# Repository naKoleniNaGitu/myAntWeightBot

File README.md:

# myAntWeightBot

## Sources

### Controler 
I decided to go with ESP32-S3 develoment module for control flexibility and BT connectivity.

* [waveshare.com product esp32-s3-zero.htm](https://www.waveshare.com/product/mcu-tools/development-boards/esp32/esp32-s3-zero.htm)
* [ESP32 S3 zero wiki](https://www.waveshare.com/wiki/ESP32-S3-Zero)

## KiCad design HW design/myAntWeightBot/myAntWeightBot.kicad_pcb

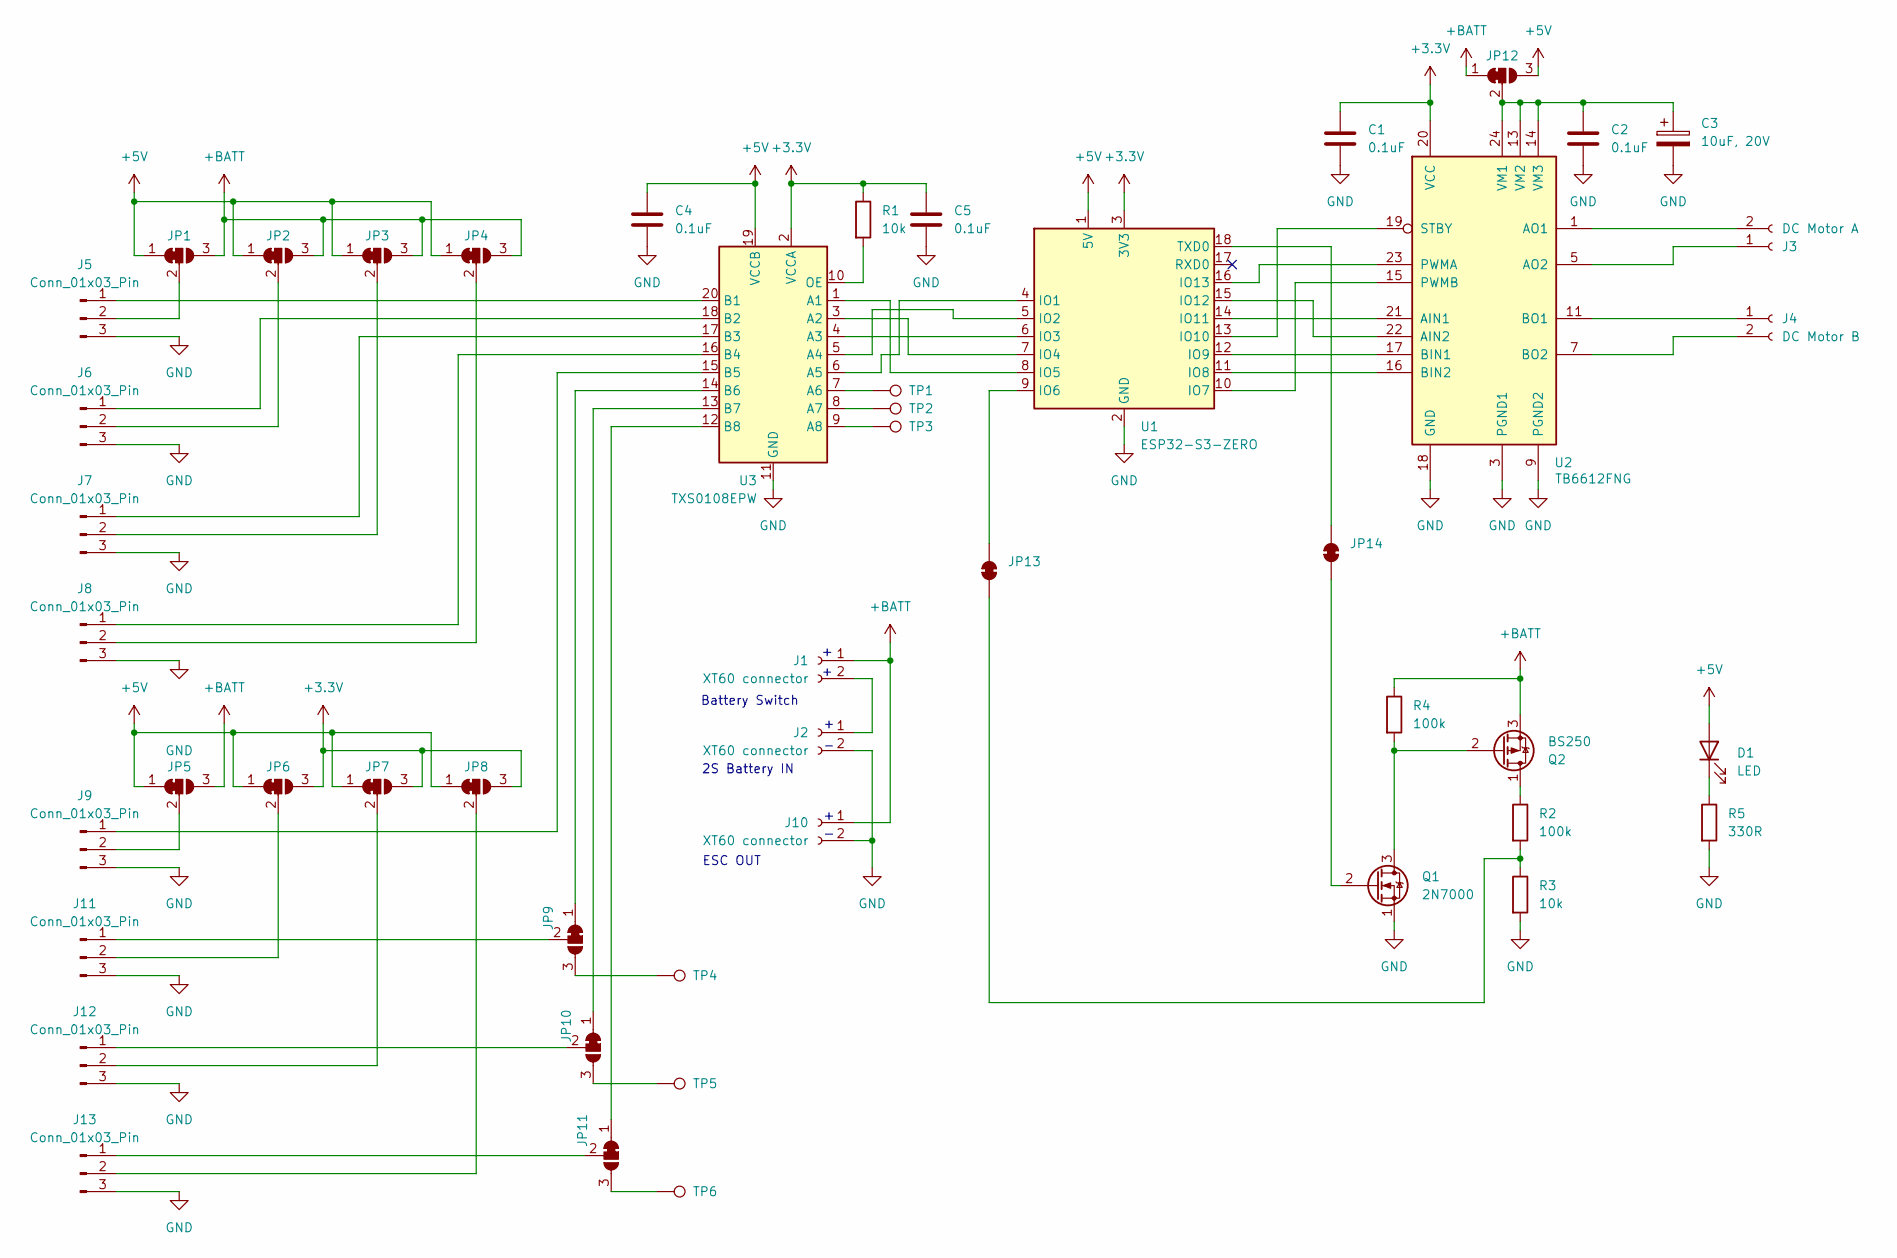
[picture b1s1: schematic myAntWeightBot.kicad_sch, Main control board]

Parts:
C1, C2, C4, C5: 0.1uF; C_0805_2012Metric
C3: 10uF, 20V; CP_EIA-6032-20_AVX-F
D1: LED; LED_D5.0mm
J1, J10: XT60 connector; XT60-F_1x02_P7.20mm_Horizontal_SMD
J2: XT60 connector; XT60-M_1x02_P7.20mm_Horizontal_SMD
J3: DC Motor A; PinHeader_1x02_P2.54mm_Vertical
J4: DC Motor B; PinHeader_1x02_P2.54mm_Vertical
J5, J6, J7, J8, J9, J11, J12, J13: Conn_01x03_Pin; PinHeader_1x03_P2.54mm_Vertical
JP1, JP2, JP3, JP4, JP5, JP6, JP7, JP8, JP9, JP10, JP11, JP12: SolderJumper_3_Bridged12; SolderJumper-3_P1.3mm_Bridged12_Pad1.0x1.5mm
JP13, JP14: SolderJumper_2_Bridged; SolderJumper-2_P1.3mm_Bridged_Pad1.0x1.5mm
Q1: 2N7000; TO-92_Inline_W4.0mm_Horizontal_FlatSideDown
Q2: BS250; TO-92_Inline_W4.0mm_Horizontal_FlatSideDown
R1, R3: 10k; R_0805_2012Metric
R2, R4: 100k; R_0805_2012Metric
R5: 330R; R_0805_2012Metric
TP1, TP2, TP3, TP4, TP5, TP6: TestPoint; TestPoint_THTPad_D1.5mm_Drill0.7mm
U1: ESP32-S3-ZERO
U2: TB6612FNG; SSOP-24_5.3x8.2mm_P0.65mm
U3: TXS0108EPW; TSSOP-20_4.4x6.5mm_P0.65mm

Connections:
+3.3V: C1.1, C5.1, JP6.3 (B), JP7.3 (B), JP8.3 (B), R1.1, U1.3 (3V3), U2.20 (VCC), U3.2 (VCCA)
+5V: C4.1, D1.2 (A), JP1.1 (A), JP2.1 (A), JP3.1 (A), JP4.1 (A), JP5.1 (A), JP6.1 (A), JP7.1 (A), JP8.1 (A), JP12.3 (B), U1.1 (5V), U3.19 (VCCB)
+BATT: J1.1, J10.1, JP1.3 (B), JP2.3 (B), JP3.3 (B), JP4.3 (B), JP5.3 (B), JP12.1 (A), Q2.3 (S), R4.1
GND: C1.2, C2.2, C3.2, C4.2, C5.2, J2.2, J5.3, J6.3, J7.3, J8.3, J9.3, J10.2, J11.3, J12.3, J13.3, Q1.1 (S), R3.2, R5.2, U1.2 (GND), U2.3 (PGND1), U2.4 (PGND1), U2.9 (PGND2), U2.10 (PGND2), U2.18 (GND), U3.11 (GND)
unnamed: D1.1 (K), R5.1
unnamed: J1.2, J2.1
unnamed: J3.1, U2.5 (AO2), U2.6 (AO2)
unnamed: J3.2, U2.1 (AO1), U2.2 (AO1)
unnamed: J4.1, U2.11 (BO1), U2.12 (BO1)
unnamed: J4.2, U2.7 (BO2), U2.8 (BO2)
unnamed: J5.1, U3.20 (B1)
unnamed: J5.2, JP1.2 (C)
unnamed: J6.1, U3.18 (B2)
unnamed: J6.2, JP2.2 (C)
unnamed: J7.1, U3.17 (B3)
unnamed: J7.2, JP3.2 (C)
unnamed: J8.1, U3.16 (B4)
unnamed: J8.2, JP4.2 (C)
unnamed: J9.1, U3.15 (B5)
unnamed: J9.2, JP5.2 (C)
unnamed: J11.1, JP9.2 (C)
unnamed: J11.2, JP6.2 (C)
unnamed: J12.1, JP10.2 (C)
unnamed: J12.2, JP7.2 (C)
unnamed: J13.1, JP11.2 (C)
unnamed: J13.2, JP8.2 (C)
unnamed: JP9.1 (A), U3.14 (B6)
unnamed: JP9.3 (B), TP4.1
unnamed: JP10.1 (A), U3.13 (B7)
unnamed: JP10.3 (B), TP5.1
unnamed: JP11.1 (A), U3.12 (B8)
unnamed: JP11.3 (B), TP6.1
unnamed: C2.1, C3.1, JP12.2 (C), U2.13 (VM2), U2.14 (VM3), U2.24 (VM1)
unnamed: JP13.1 (A), R2.2, R3.1
unnamed: JP13.2 (B), U1.9 (IO6)
unnamed: JP14.1 (A), Q1.2 (G)
unnamed: JP14.2 (B), U1.18 (TXD0)
unnamed: Q1.3 (D), Q2.2 (G), R4.2
unnamed: Q2.1 (D), R2.1
unnamed: U1.4 (IO1), U3.6 (A5)
unnamed: U1.5 (IO2), U3.5 (A4)
unnamed: U1.6 (IO3), U3.4 (A3)
unnamed: U1.7 (IO4), U3.3 (A2)
unnamed: U1.8 (IO5), U3.1 (A1)
unnamed: U1.10 (IO7), U2.15 (PWMB)
unnamed: U1.11 (IO8), U2.16 (BIN2)
unnamed: U1.12 (IO9), U2.17 (BIN1)
unnamed: U1.13 (IO10), U2.19 (STBY)
unnamed: U1.14 (IO11), U2.21 (AIN1)
unnamed: U1.15 (IO12), U2.22 (AIN2)
unnamed: U1.16 (IO13), U2.23 (PWMA)
unnamed: TP1.1, U3.7 (A6)
unnamed: TP2.1, U3.8 (A7)
unnamed: TP3.1, U3.9 (A8)
unnamed: R1.2, U3.10 (OE)

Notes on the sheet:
2S Battery IN
Battery Switch
ESC OUT

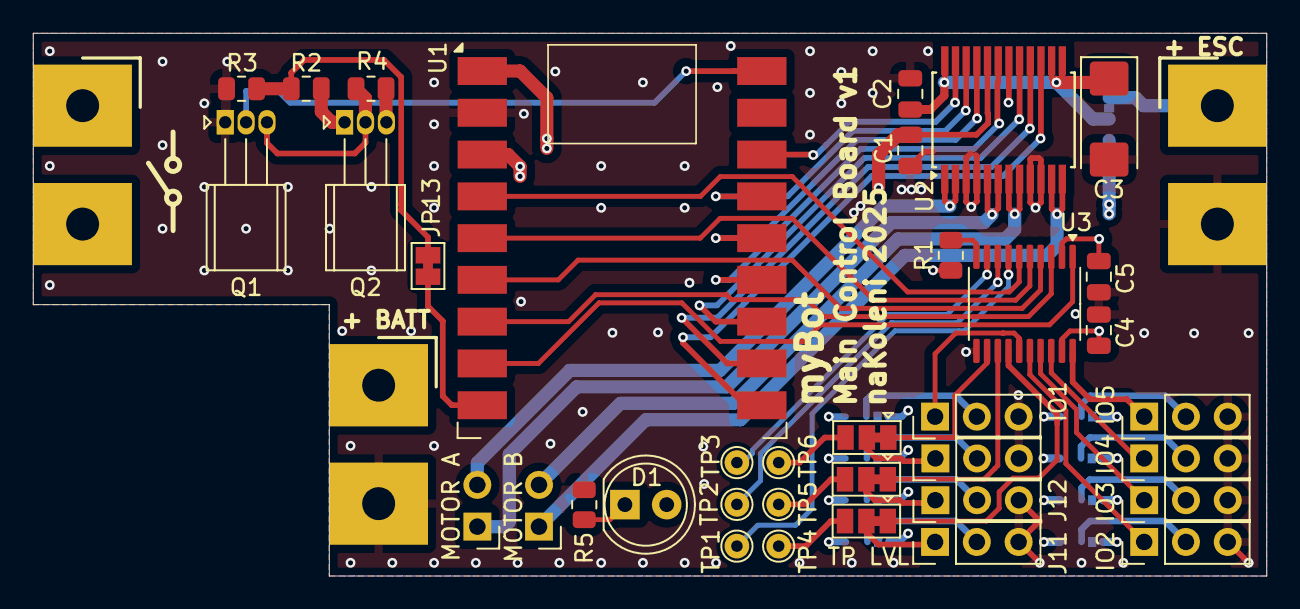
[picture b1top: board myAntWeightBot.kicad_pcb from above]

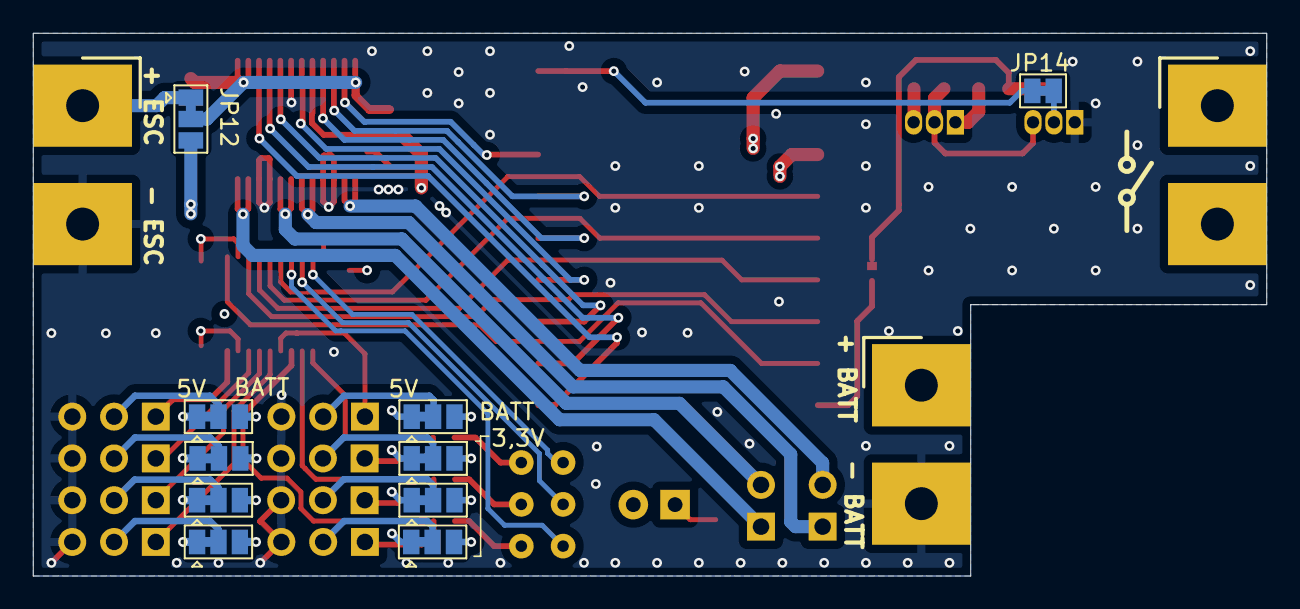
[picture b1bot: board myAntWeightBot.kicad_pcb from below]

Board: 4 copper layers, 75.0 x 33.0 mm, 49 parts (11 on the bottom side), 55 nets.

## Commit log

2024-09-05 Initial base code
2024-09-05 not tested propultion controll
2024-09-10 working foundatiton tested with one motor
2025-11-14 all old
2025-11-14 initial config
2025-11-14 3rd party lib
2025-11-15 battery meas and telemetry
